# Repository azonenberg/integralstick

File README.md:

# integralstick
STM32F7 + Artix-7 SoM

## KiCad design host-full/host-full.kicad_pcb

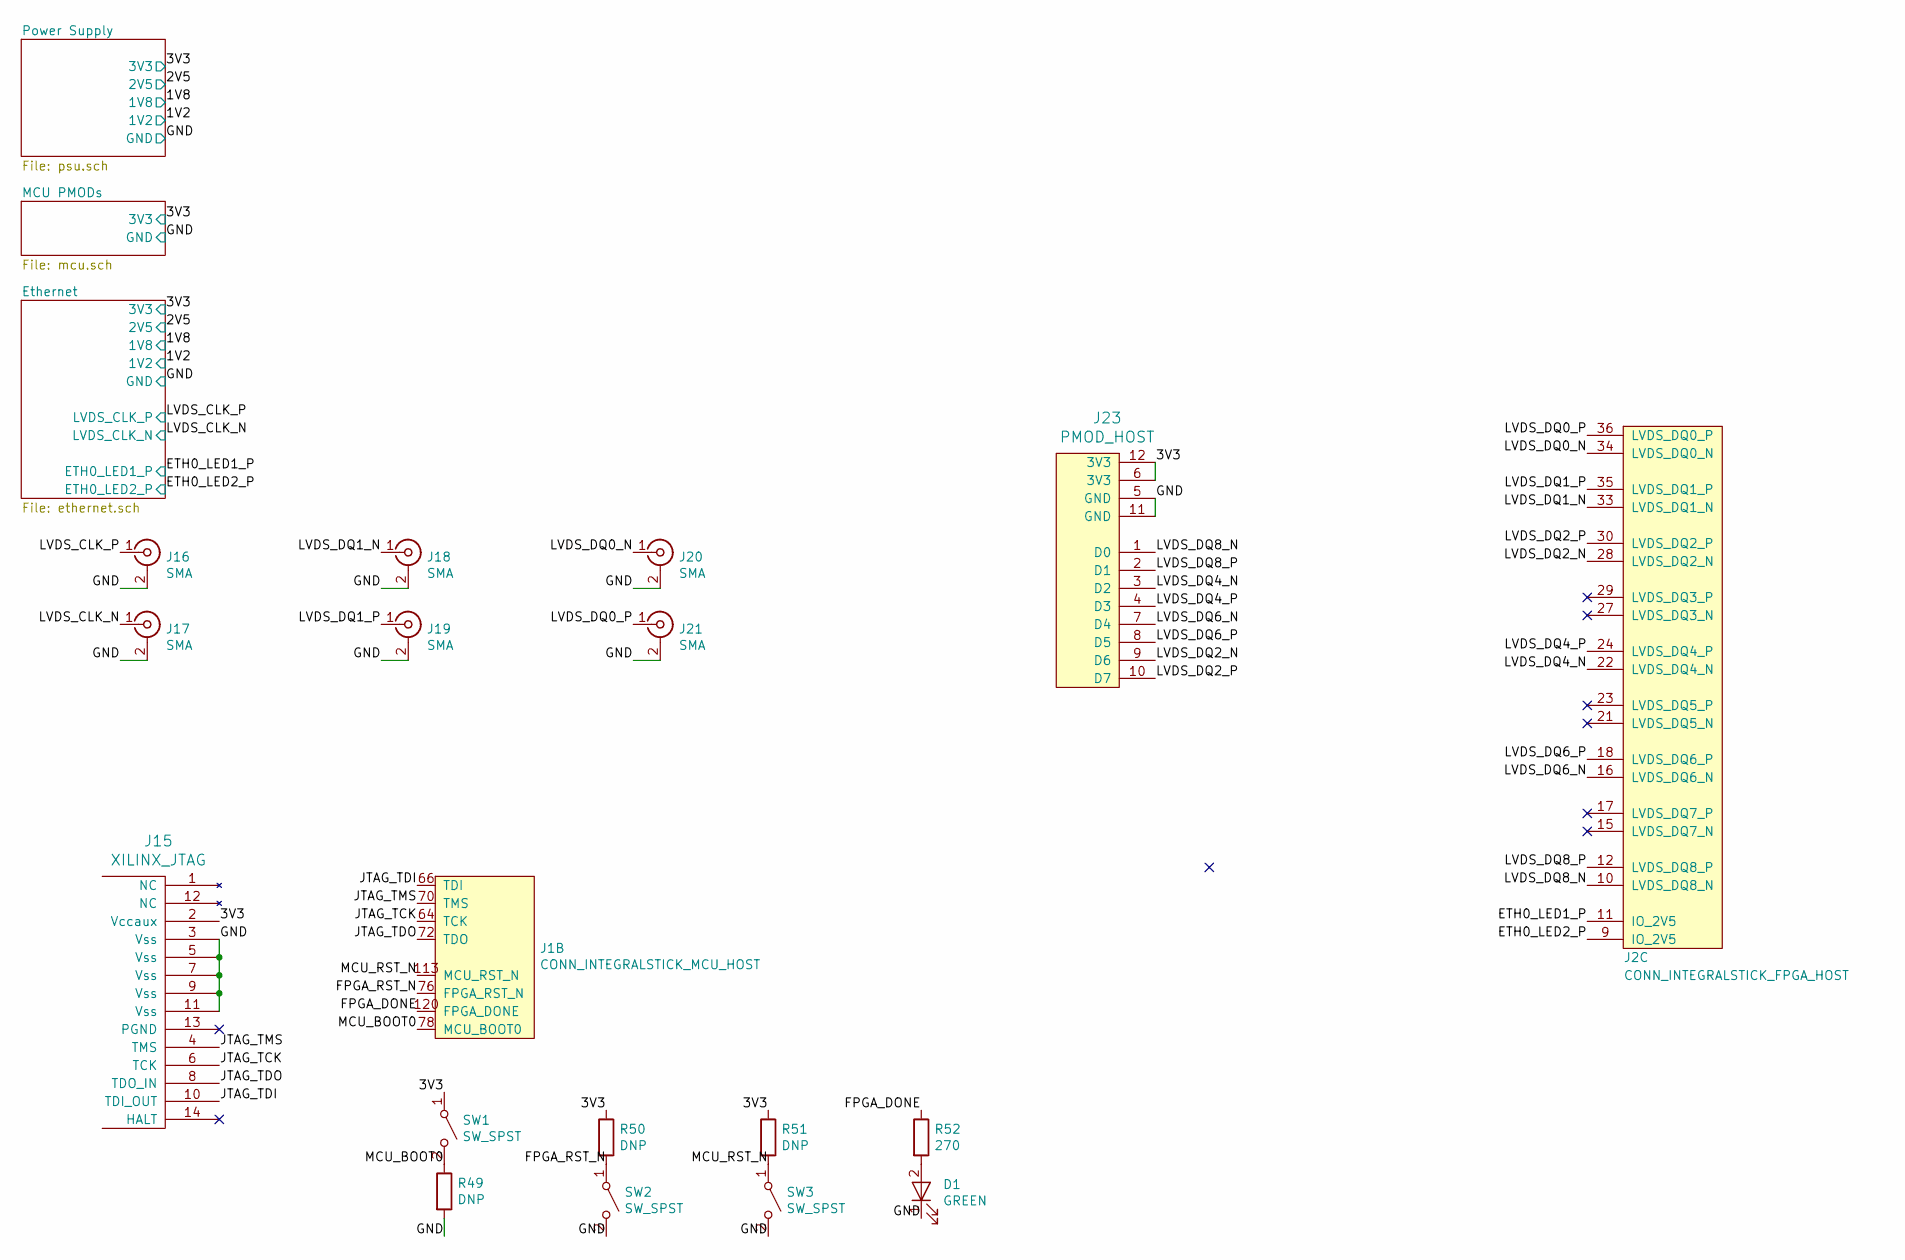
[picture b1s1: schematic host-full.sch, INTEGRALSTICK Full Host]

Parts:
D1: GREEN; EIA_0603_LED
J1: CONN_INTEGRALSTICK_MCU_HOST; CONN_SAMTEC_QSH-060-01-L-D-A
J2: CONN_INTEGRALSTICK_FPGA_HOST; CONN_SAMTEC_QSH-060-01-L-D-A
J15: XILINX_JTAG; XILINX_JTAG_PTH_MOLEX_0878311420
J16, J17, J18, J19, J20, J21: SMA; CONN_SMA_EDGE_SAMTEC_SMA_J_P_H_ST_EM1
J23: PMOD_HOST; CONN_HEADER_2.54MM_2x6_RA_PMOD_HOST
R49, R50, R51: DNP; EIA_0402_RES_NOSILK
R52: 270; EIA_0402_RES_NOSILK
SW1, SW2, SW3: SW_SPST; SWITCH_RAFI_MICON_5

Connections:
/3V3: J15.2 (Vccaux), J23.6 (3V3), J23.12 (3V3), R50.1, R51.1, SW1.1 (A); also elsewhere on the board
/ETH0_LED1_P: J2.11 (IO_2V5); also elsewhere on the board
/ETH0_LED2_P: J2.9 (IO_2V5); also elsewhere on the board
/FPGA_DONE: J1.120 (FPGA_DONE), R52.1
/FPGA_RST_N: J1.76 (FPGA_RST_N), R50.2, SW2.1 (A)
/GND: D1.1 (K), J15.3 (Vss), J15.5 (Vss), J15.7 (Vss), J15.9 (Vss), J15.11 (Vss), J16.2 (Ext), J17.2 (Ext), J18.2 (Ext), J19.2 (Ext), J20.2 (Ext), J21.2 (Ext), J23.5 (GND), J23.11 (GND), R49.2, SW2.2 (B), SW3.2 (B); also elsewhere on the board
/JTAG_TCK: J1.64 (TCK), J15.6 (TCK)
/JTAG_TDI: J1.66 (TDI), J15.10 (TDI_OUT)
/JTAG_TDO: J1.72 (TDO), J15.8 (TDO_IN)
/JTAG_TMS: J1.70 (TMS), J15.4 (TMS)
/LVDS_CLK_N: J17.1 (In); also elsewhere on the board
/LVDS_CLK_P: J16.1 (In); also elsewhere on the board
/LVDS_DQ0_N: J2.34 (LVDS_DQ0_N), J20.1 (In)
/LVDS_DQ0_P: J2.36 (LVDS_DQ0_P), J21.1 (In)
/LVDS_DQ1_N: J2.33 (LVDS_DQ1_N), J18.1 (In)
/LVDS_DQ1_P: J2.35 (LVDS_DQ1_P), J19.1 (In)
/LVDS_DQ2_N: J2.28 (LVDS_DQ2_N), J23.9 (D6)
/LVDS_DQ2_P: J2.30 (LVDS_DQ2_P), J23.10 (D7)
/LVDS_DQ4_N: J2.22 (LVDS_DQ4_N), J23.3 (D2)
/LVDS_DQ4_P: J2.24 (LVDS_DQ4_P), J23.4 (D3)
/LVDS_DQ6_N: J2.16 (LVDS_DQ6_N), J23.7 (D4)
/LVDS_DQ6_P: J2.18 (LVDS_DQ6_P), J23.8 (D5)
/LVDS_DQ8_N: J2.10 (LVDS_DQ8_N), J23.1 (D0)
/LVDS_DQ8_P: J2.12 (LVDS_DQ8_P), J23.2 (D1)
/MCU_BOOT0: J1.78 (MCU_BOOT0), R49.1, SW1.2 (B)
/MCU_RST_N: J1.113 (MCU_RST_N), R51.2, SW3.1 (A)
unnamed: D1.2 (A), R52.2

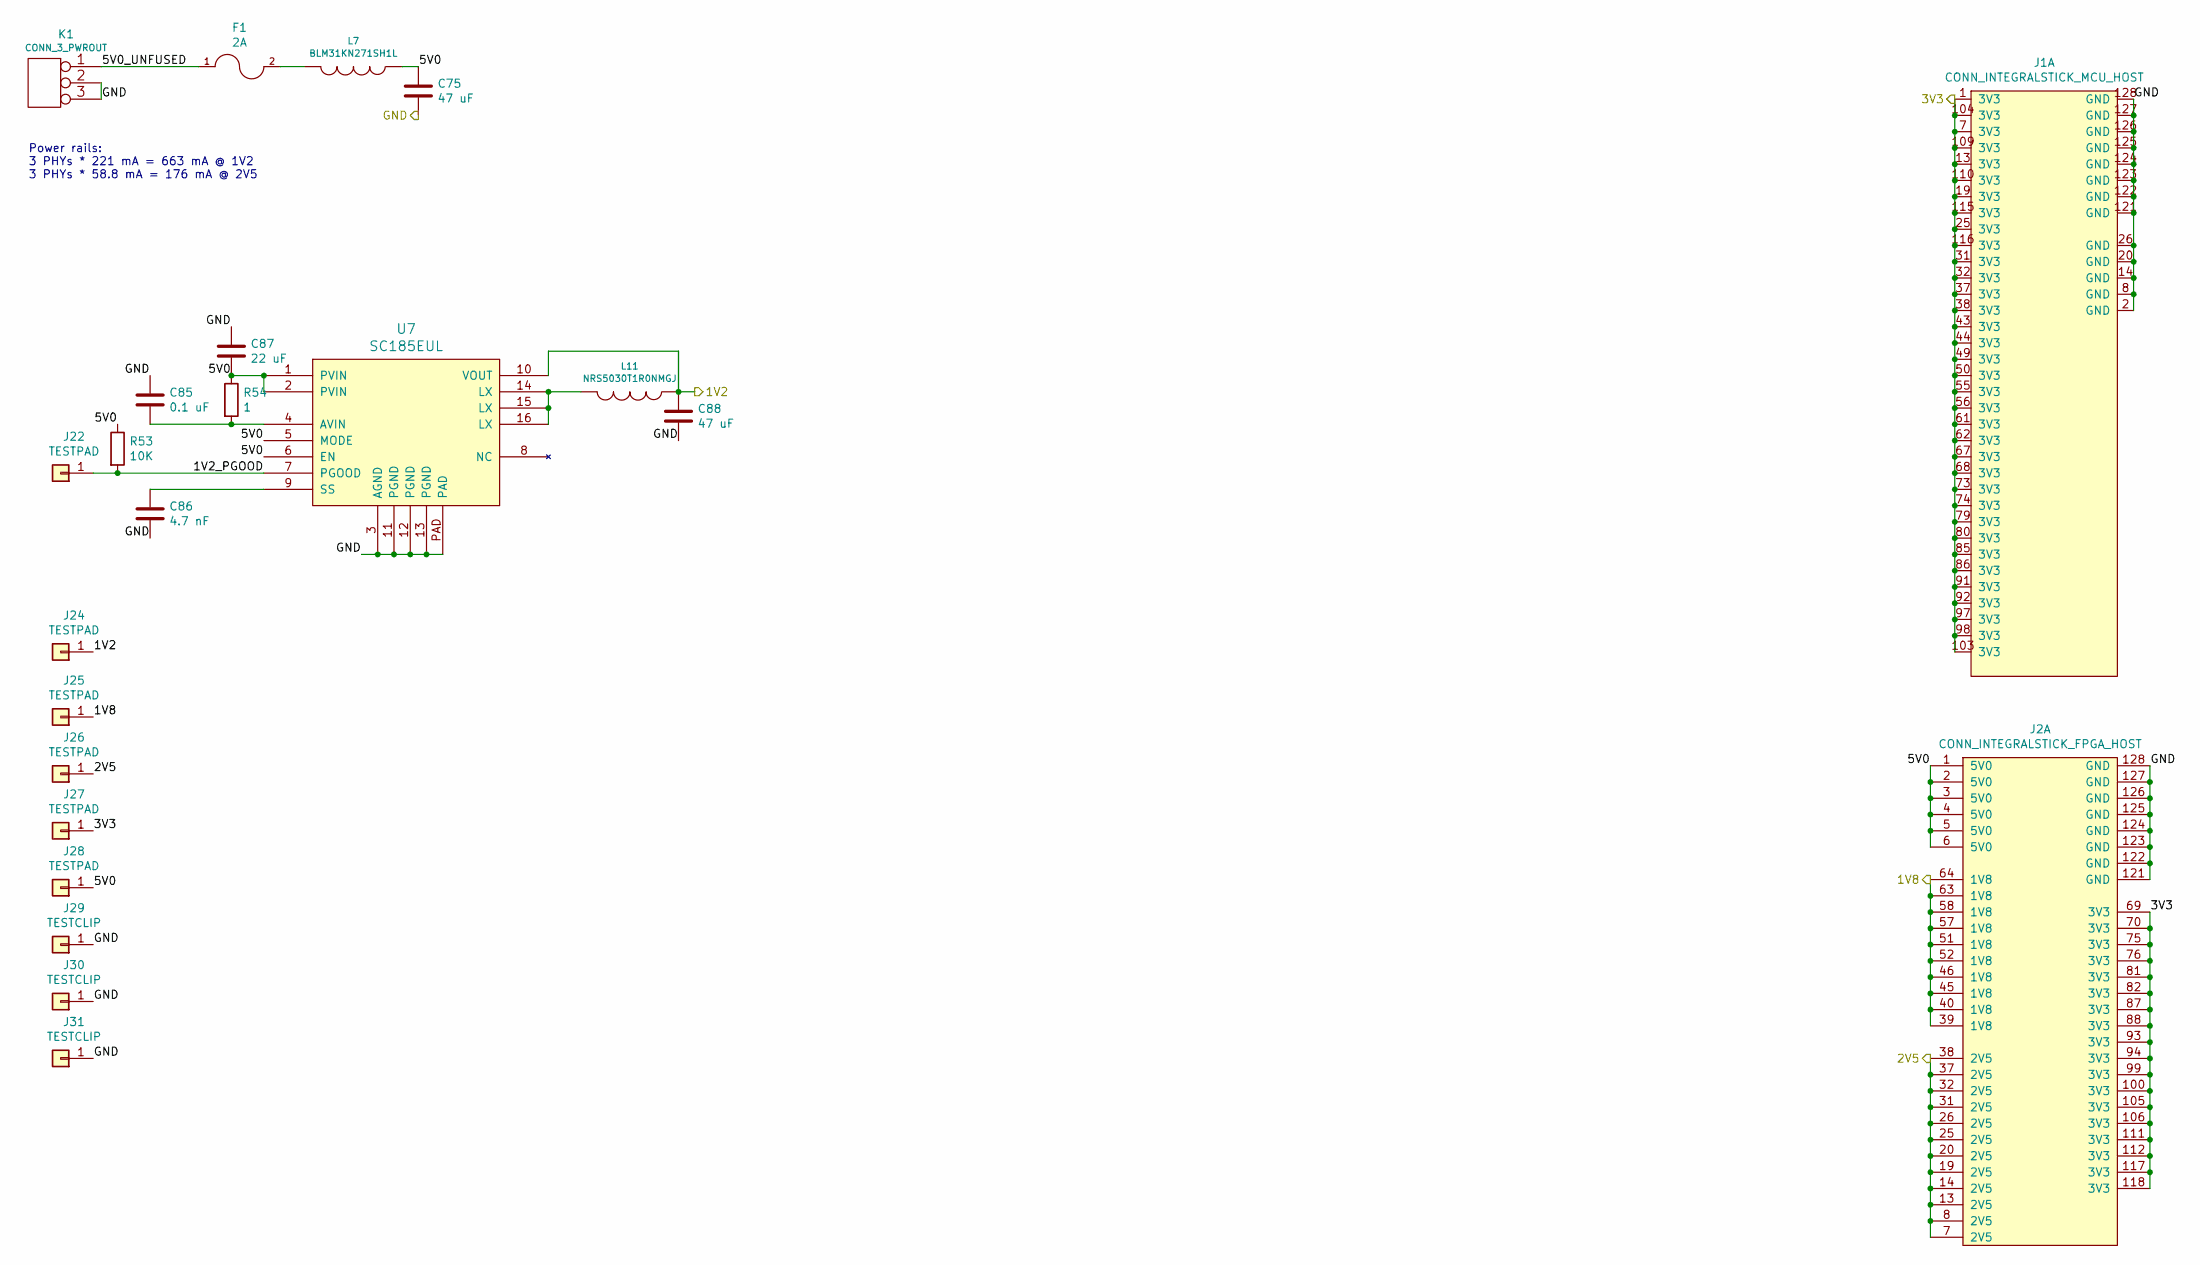
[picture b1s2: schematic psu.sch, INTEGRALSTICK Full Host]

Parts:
C75, C88: 47 uF; EIA_1210_CAP_NOSILK
C85: 0.1 uF; EIA_0402_CAP_NOSILK
C86: 4.7 nF; EIA_0603_CAP_NOSILK
C87: 22 uF; EIA_1210_CAP_NOSILK
F1: 2A; EIA_0603_RES_NOSILK
J1: CONN_INTEGRALSTICK_MCU_HOST; CONN_SAMTEC_QSH-060-01-L-D-A
J2: CONN_INTEGRALSTICK_FPGA_HOST; CONN_SAMTEC_QSH-060-01-L-D-A
J22, J24, J25, J26, J27, J28: TESTPAD; TESTPOINT_SMT_0.5MM
J29, J30, J31: TESTCLIP; TESTPOINT_SMT_KEYSTONE_5016
K1: CONN_3_PWROUT; CONN_CUI_PJ-058BH_HIPWR_BARREL_NOSLOT
L7: BLM31KN271SH1L; EIA_1206_CAP_NOSILK
L11: NRS5030T1R0NMGJ; INDUCTOR_YUDEN_NRS5030
R53: 10K; EIA_0402_RES_NOSILK
R54: 1; EIA_0402_RES_NOSILK
U7: SC185EUL; QFN_16_0.5MM_3x3MM

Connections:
/1V2: C88.1, J24.1, L11.1, U7.10 (VOUT); also elsewhere on the board
/1V8: J2.39 (1V8), J2.40 (1V8), J2.45 (1V8), J2.46 (1V8), J2.51 (1V8), J2.52 (1V8), J2.57 (1V8), J2.58 (1V8), J2.63 (1V8), J2.64 (1V8), J25.1; also elsewhere on the board
/2V5: J2.7 (2V5), J2.8 (2V5), J2.13 (2V5), J2.14 (2V5), J2.19 (2V5), J2.20 (2V5), J2.25 (2V5), J2.26 (2V5), J2.31 (2V5), J2.32 (2V5), J2.37 (2V5), J2.38 (2V5), J26.1; also elsewhere on the board
/3V3: J1.1 (3V3), J1.7 (3V3), J1.13 (3V3), J1.19 (3V3), J1.25 (3V3), J1.31 (3V3), J1.32 (3V3), J1.37 (3V3), J1.38 (3V3), J1.43 (3V3), J1.44 (3V3), J1.49 (3V3), J1.50 (3V3), J1.55 (3V3), J1.56 (3V3), J1.61 (3V3), J1.62 (3V3), J1.67 (3V3), J1.68 (3V3), J1.73 (3V3), J1.74 (3V3), J1.79 (3V3), J1.80 (3V3), J1.85 (3V3), J1.86 (3V3), J1.91 (3V3), J1.92 (3V3), J1.97 (3V3), J1.98 (3V3), J1.103 (3V3), J1.104 (3V3), J1.109 (3V3), J1.110 (3V3), J1.115 (3V3), J1.116 (3V3), J2.69 (3V3), J2.70 (3V3), J2.75 (3V3), J2.76 (3V3), J2.81 (3V3), J2.82 (3V3), J2.87 (3V3), J2.88 (3V3), J2.93 (3V3), J2.94 (3V3), J2.99 (3V3), J2.100 (3V3), J2.105 (3V3), J2.106 (3V3), J2.111 (3V3), J2.112 (3V3), J2.117 (3V3), J2.118 (3V3), J27.1; also elsewhere on the board
/GND: C75.2, C85.1, C86.2, C87.1, C88.2, J1.2 (GND), J1.8 (GND), J1.14 (GND), J1.20 (GND), J1.26 (GND), J1.121 (GND), J1.122 (GND), J1.123 (GND), J1.124 (GND), J1.125 (GND), J1.126 (GND), J1.127 (GND), J1.128 (GND), J2.121 (GND), J2.122 (GND), J2.123 (GND), J2.124 (GND), J2.125 (GND), J2.126 (GND), J2.127 (GND), J2.128 (GND), J29.1, J30.1, J31.1, K1.2 (PM), K1.3, U7.3 (AGND), U7.11 (PGND), U7.12 (PGND), U7.13 (PGND), U7.PAD; also elsewhere on the board
/Power Supply/1V2_PGOOD: J22.1, R53.2, U7.7 (PGOOD)
/Power Supply/5V0: C75.1, C87.2, J2.1 (5V0), J2.2 (5V0), J2.3 (5V0), J2.4 (5V0), J2.5 (5V0), J2.6 (5V0), J28.1, L7.1, R53.1, R54.1, U7.1 (PVIN), U7.2 (PVIN), U7.5 (MODE), U7.6 (EN)
/Power Supply/5V0_UNFUSED: F1.1, K1.1
unnamed: C85.2, R54.2, U7.4 (AVIN)
unnamed: C86.1, U7.9 (SS)
unnamed: F1.2, L7.2
unnamed: L11.2, U7.14 (LX), U7.15 (LX), U7.16 (LX)

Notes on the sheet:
Power rails: 3 PHYs * 221 mA = 663 mA @ 1V2 3 PHYs * 58.8 mA = 176 mA @ 2V5

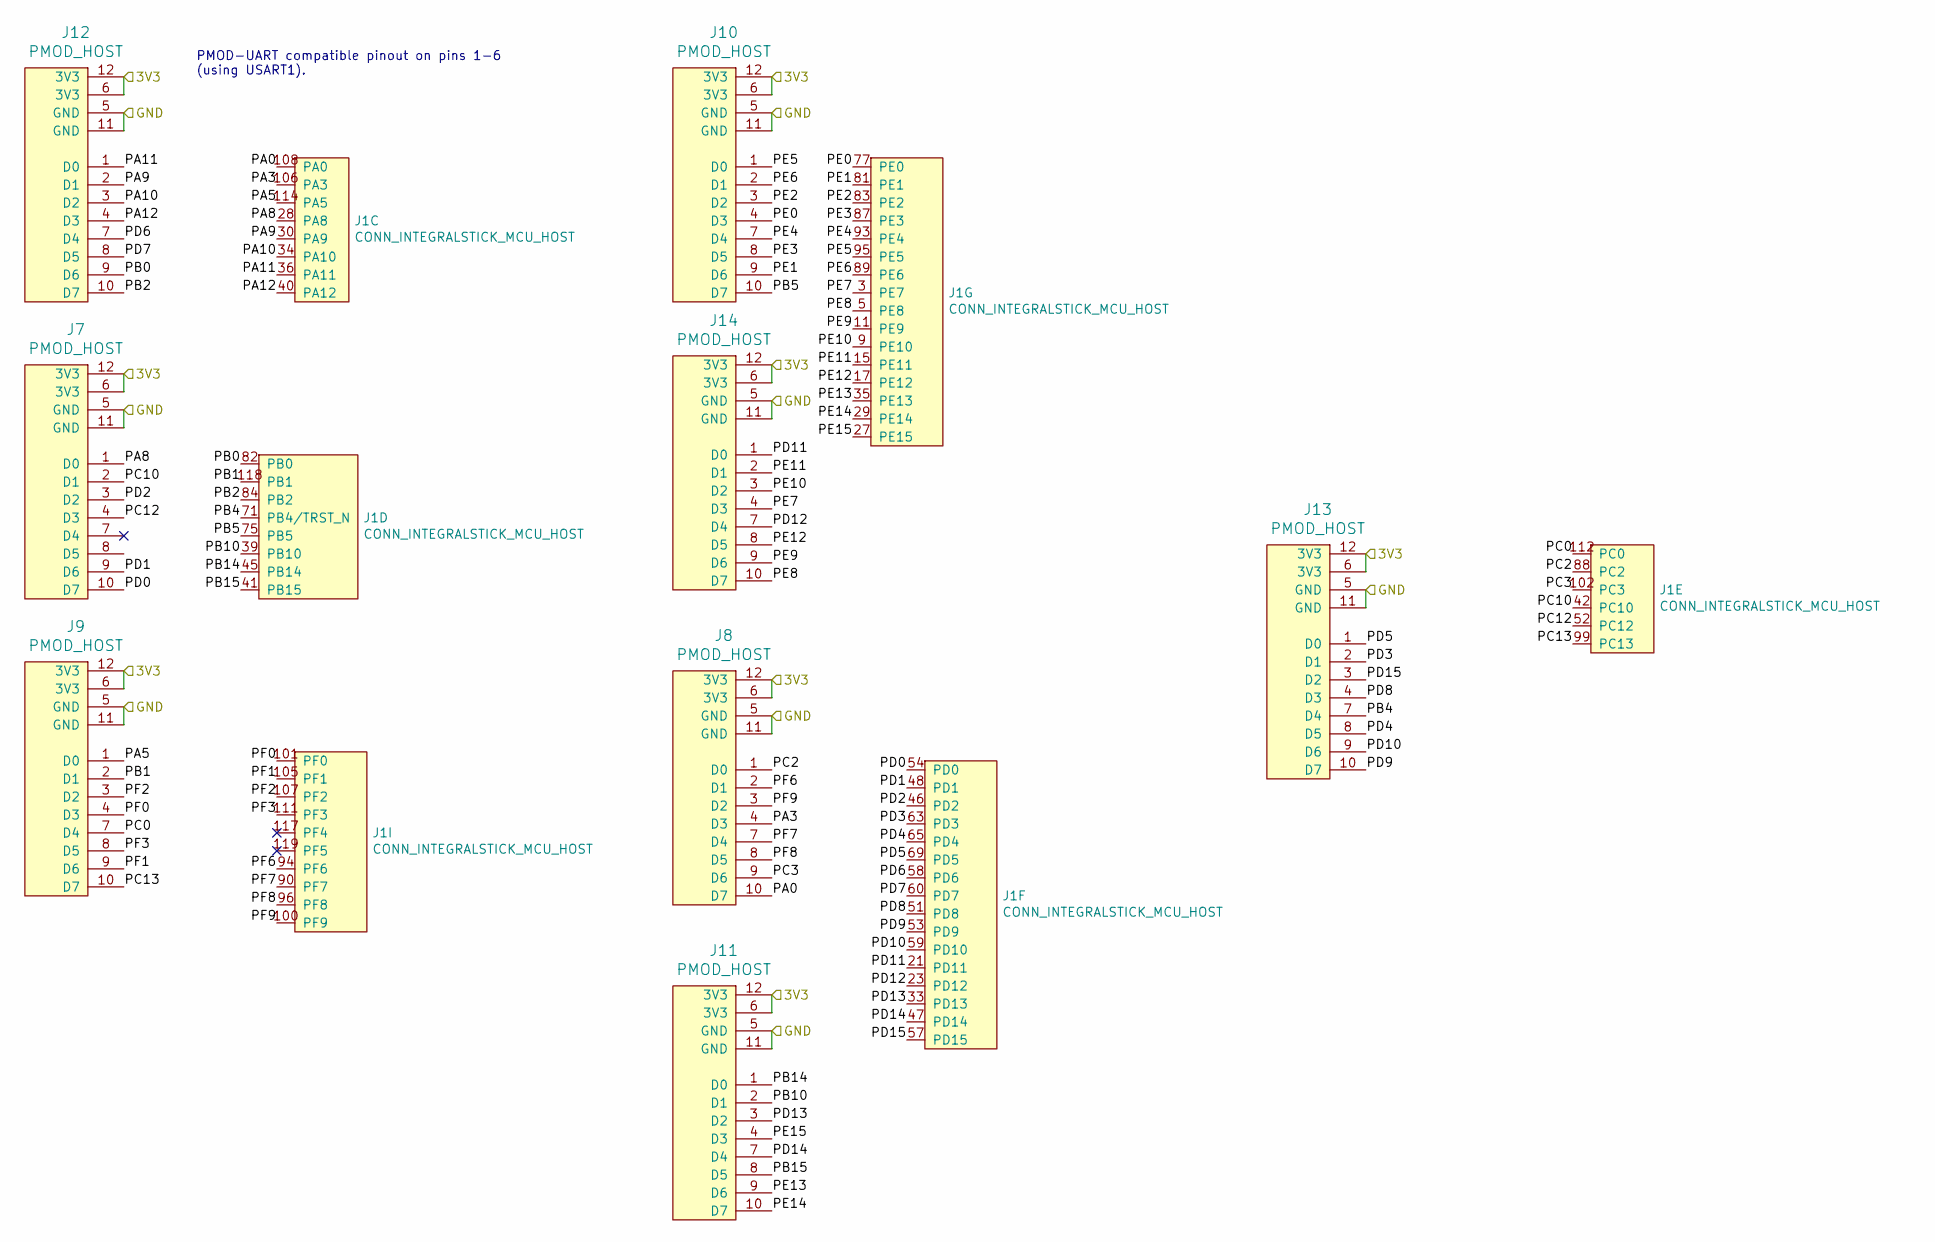
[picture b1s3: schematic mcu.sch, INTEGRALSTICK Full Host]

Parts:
J1: CONN_INTEGRALSTICK_MCU_HOST; CONN_SAMTEC_QSH-060-01-L-D-A
J7, J8, J9, J10, J11, J12, J13, J14: PMOD_HOST; CONN_HEADER_2.54MM_2x6_RA_PMOD_HOST

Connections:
/3V3: J7.6 (3V3), J7.12 (3V3), J8.6 (3V3), J8.12 (3V3), J9.6 (3V3), J9.12 (3V3), J10.6 (3V3), J10.12 (3V3), J11.6 (3V3), J11.12 (3V3), J12.6 (3V3), J12.12 (3V3), J13.6 (3V3), J13.12 (3V3), J14.6 (3V3), J14.12 (3V3); also elsewhere on the board
/GND: J7.5 (GND), J7.11 (GND), J8.5 (GND), J8.11 (GND), J9.5 (GND), J9.11 (GND), J10.5 (GND), J10.11 (GND), J11.5 (GND), J11.11 (GND), J12.5 (GND), J12.11 (GND), J13.5 (GND), J13.11 (GND), J14.5 (GND), J14.11 (GND); also elsewhere on the board
/MCU PMODs/PA0: J1.108 (PA0), J8.10 (D7)
/MCU PMODs/PA3: J1.106 (PA3), J8.4 (D3)
/MCU PMODs/PA5: J1.114 (PA5), J9.1 (D0)
/MCU PMODs/PA8: J1.28 (PA8), J7.1 (D0)
/MCU PMODs/PA9: J1.30 (PA9), J12.2 (D1)
/MCU PMODs/PA10: J1.34 (PA10), J12.3 (D2)
/MCU PMODs/PA11: J1.36 (PA11), J12.1 (D0)
/MCU PMODs/PA12: J1.40 (PA12), J12.4 (D3)
/MCU PMODs/PB0: J1.82 (PB0), J12.9 (D6)
/MCU PMODs/PB1: J1.118 (PB1), J9.2 (D1)
/MCU PMODs/PB2: J1.84 (PB2), J12.10 (D7)
/MCU PMODs/PB4: J1.71 (PB4/TRST_N), J13.7 (D4)
/MCU PMODs/PB5: J1.75 (PB5), J10.10 (D7)
/MCU PMODs/PB10: J1.39 (PB10), J11.2 (D1)
/MCU PMODs/PB14: J1.45 (PB14), J11.1 (D0)
/MCU PMODs/PB15: J1.41 (PB15), J11.8 (D5)
/MCU PMODs/PC0: J1.112 (PC0), J9.7 (D4)
/MCU PMODs/PC2: J1.88 (PC2), J8.1 (D0)
/MCU PMODs/PC3: J1.102 (PC3), J8.9 (D6)
/MCU PMODs/PC10: J1.42 (PC10), J7.2 (D1)
/MCU PMODs/PC12: J1.52 (PC12), J7.4 (D3)
/MCU PMODs/PC13: J1.99 (PC13), J9.10 (D7)
/MCU PMODs/PD0: J1.54 (PD0), J7.10 (D7)
/MCU PMODs/PD1: J1.48 (PD1), J7.9 (D6)
/MCU PMODs/PD2: J1.46 (PD2), J7.3 (D2)
/MCU PMODs/PD3: J1.63 (PD3), J13.2 (D1)
/MCU PMODs/PD4: J1.65 (PD4), J13.8 (D5)
/MCU PMODs/PD5: J1.69 (PD5), J13.1 (D0)
/MCU PMODs/PD6: J1.58 (PD6), J12.7 (D4)
/MCU PMODs/PD7: J1.60 (PD7), J12.8 (D5)
/MCU PMODs/PD8: J1.51 (PD8), J13.4 (D3)
/MCU PMODs/PD9: J1.53 (PD9), J13.10 (D7)
/MCU PMODs/PD10: J1.59 (PD10), J13.9 (D6)
/MCU PMODs/PD11: J1.21 (PD11), J14.1 (D0)
/MCU PMODs/PD12: J1.23 (PD12), J14.7 (D4)
/MCU PMODs/PD13: J1.33 (PD13), J11.3 (D2)
/MCU PMODs/PD14: J1.47 (PD14), J11.7 (D4)
/MCU PMODs/PD15: J1.57 (PD15), J13.3 (D2)
/MCU PMODs/PE0: J1.77 (PE0), J10.4 (D3)
/MCU PMODs/PE1: J1.81 (PE1), J10.9 (D6)
/MCU PMODs/PE2: J1.83 (PE2), J10.3 (D2)
/MCU PMODs/PE3: J1.87 (PE3), J10.8 (D5)
/MCU PMODs/PE4: J1.93 (PE4), J10.7 (D4)
/MCU PMODs/PE5: J1.95 (PE5), J10.1 (D0)
/MCU PMODs/PE6: J1.89 (PE6), J10.2 (D1)
/MCU PMODs/PE7: J1.3 (PE7), J14.4 (D3)
/MCU PMODs/PE8: J1.5 (PE8), J14.10 (D7)
/MCU PMODs/PE9: J1.11 (PE9), J14.9 (D6)
/MCU PMODs/PE10: J1.9 (PE10), J14.3 (D2)
/MCU PMODs/PE11: J1.15 (PE11), J14.2 (D1)
/MCU PMODs/PE12: J1.17 (PE12), J14.8 (D5)
/MCU PMODs/PE13: J1.35 (PE13), J11.9 (D6)
/MCU PMODs/PE14: J1.29 (PE14), J11.10 (D7)
/MCU PMODs/PE15: J1.27 (PE15), J11.4 (D3)
/MCU PMODs/PF0: J1.101 (PF0), J9.4 (D3)
/MCU PMODs/PF1: J1.105 (PF1), J9.9 (D6)
/MCU PMODs/PF2: J1.107 (PF2), J9.3 (D2)
/MCU PMODs/PF3: J1.111 (PF3), J9.8 (D5)
/MCU PMODs/PF6: J1.94 (PF6), J8.2 (D1)
/MCU PMODs/PF7: J1.90 (PF7), J8.7 (D4)
/MCU PMODs/PF8: J1.96 (PF8), J8.8 (D5)
/MCU PMODs/PF9: J1.100 (PF9), J8.3 (D2)

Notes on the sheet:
PMOD-UART compatible pinout on pins 1-6 (using USART1).
